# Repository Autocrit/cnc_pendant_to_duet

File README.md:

# CNC Pendant D-Sub connector to Duet PCB

## Overview

The aim for this PCB was to simplify the connection of a CNC pendant to a Duet 2 or 3, and to provide a disconnect at the electronics enclosure.

It follows the wiring diagram and instructions at [Duet3D CNC Pendant Documentation](https://docs.duet3d.com/User_manual/Connecting_hardware/IO_CNC_Pendant).

## Notes

1. Other CNC pendants may have different pin arrangements. Some differences could be fixed in firmware; others only by modifying the PCB.
1. This PCB was tested with a Duet 3, but not with a Duet 2 or a PanelDue.
1. There is a small change needed to the Arduino firmware. 
1. I don't know what I'm doing. Use at your own risk.
1. There's a pin labelled *iO.out* on the PCB in these photos. That's a mistake and its corrected to *dout* in the KiCad project.

## Ordering

Production files are at `./kicad/production/cnc_pendant_to_duet.zip`. In February 2026, 5 boards from JLCPCB cost £3.60 including VAT and delivery to the UK.

## Choice of CNC pendant

I have [this](https://www.aliexpress.com/item/32847286243.html) pendant from [Rattm Motor Store](https://www.aliexpress.com/store/907217) on Aliexpress (the listing says 4-axis but the one I received is 5-axis).

### D-Sub pins

The image below shows a female socket as you look at it:

GND, COM-, and shield are all connected to ground on the PCB.

The connector pinout can be checked against the pads in the pendant.

## Mounting

The PCB can be mounted to the inside of an enclosure using the hex studs of the D‑sub connector. Alternatively, it could be mounted internally with an extension cable.

### Cutout

[DXF](./cad/panel_cutout.dxf)
[PDF](./cad/panel_cutout.pdf)

### PCB dimensions and hole spacing

## Components

| Reference | Description |
|---------- | ------- |
| U1 | Arduino Pro Micro |
| R1 | 1206 SMD 6K8 (6.8kΩ) resistor |
| R2 | 1206 SMD 10K (10kΩ) resistor |
| J1 | 1x4 2.54mm pitch male right-angle (optional) header |
| J2 | 15-pin D-Sub female right-angle (optional) connector with hex screws |

### Arduino Pro Micro (U1)

Use 2 1x12 female headers if the Arduino should be removable.

### Resistors (R1 & R2)

The resistors are optional when connecting to a Duet 3. If omitted, the pads of R1 should be bridged (see image).

### 1x4 header (J1)

The 1x4 pin 2.54mm pitch male header for connecting to a Duet 2 or 3 can be any make or type; a right-angle connector keeps the height low.

Examples are Würth Elektronik WR-WTB [61900411121](https://www.we-online.com/en/components/products/WTB_WR_WTB_2_54_MALE#61900411121) (vertical), 
Würth Elektronik WR-WTB [61900411021](https://www.we-online.com/en/components/products/WTB_WR_WTB_2_54_MALE#61900411021) (horizontal) or Würth Elektronik WR-WTB [61900419521](https://www.we-online.com/en/components/products/WTB_WR_WTB_2_54_MALE#61900419521) (also horizontal).

KF2510 connectors are a cheaper alternative.

### D-Sub connector (J2)

e.g. Würth Elektronik WR-DSUB PCB [618015231121](https://www.we-online.com/en/components/products/INPUT_OUTPUT_WR_DSUB_CONNECTORS_PCB#618015231121).

The mounting‑hole‑to‑board‑edge dimension appears to be a common one; cheaper connectors from, for example, Ebay seem fine.

## Connecting to Duet 2 or 3

This image shows the PCB connected to io.0 on a Duet 3.

See [Connector and spare part numbers](https://docs.duet3d.com/User_manual/Troubleshooting/Parts).

Würth Elektronik WR-WTB 4-pin [61900411621](https://www.we-online.com/en/components/products/WTB_2_54_FEMALE_TERMINAL_HOUSING_6190XX11621#61900411621), Würth Elektronik WR-WTB 5-pin [61900511621](https://www.we-online.com/en/components/products/WTB_2_54_FEMALE_TERMINAL_HOUSING_6190XX11621#61900511621) and Würth Elektronik WR-WTB female crimp [61900113722DEC](https://www.we-online.com/en/components/products/WTB_2_54_FEMALE_CRIMP_CONTACT_619X0113722#61900113722DEC).

## Firmware

### Firmware change

In `CNC-pendant.ino`, change line 221 to:
```
distanceMultiplier = 1;
```

The reason for this is that there is no X1 pin (or signal) and the code is unable to detect that X1 is selected. Initialising `distanceMultiplier` to `1` instead of `0` solves that.

Note that the firmware is unable to control the pendant's LED (for example, to turn it off on an emergency stop) because there is no LED+ signal.

## Config

The Duet3D pendant documentation doesn't mention that serial communication needs to be enabled on io0 on Duet 3. For example:
```
; Accessories
M575 P1 S1 B57600 ; CNC pendant support
```

## Modifying the PCB for a different pinout

Anyone familiar with KiCad or PCB design should ignore this.
1. In the Schematic Editor, change labels on the DA-15 socket as necessary.
1. In the PCB Editor, *Tools->Update PCB from Schematic...*
1. Delete all vias and tracks with *Edit->Global Deletions...->Tracks & vias*
1. I would then cheat and use the *Freerouting* plugin, followed by some clean up (it  leaves unconnected tracks and other easily-fixed issues).
1. Use *Inspect->Design Rules Checker* to help find problems.
1. I used the *Fabrication Toolkit* plugin to generate files for JLCPCB. As its going to be an unassembled board, only the ZIP file is important.

I can help if you know the pinout but don't want to dive into KiCad.

## Adding a D-Sub connector to the "standard" CNC pendant

## TODO
- test with Duet 2
- test with PanelDue 
- test with more than one CNC pendant
- add pins for PanelDue wiring (if that would be useful)

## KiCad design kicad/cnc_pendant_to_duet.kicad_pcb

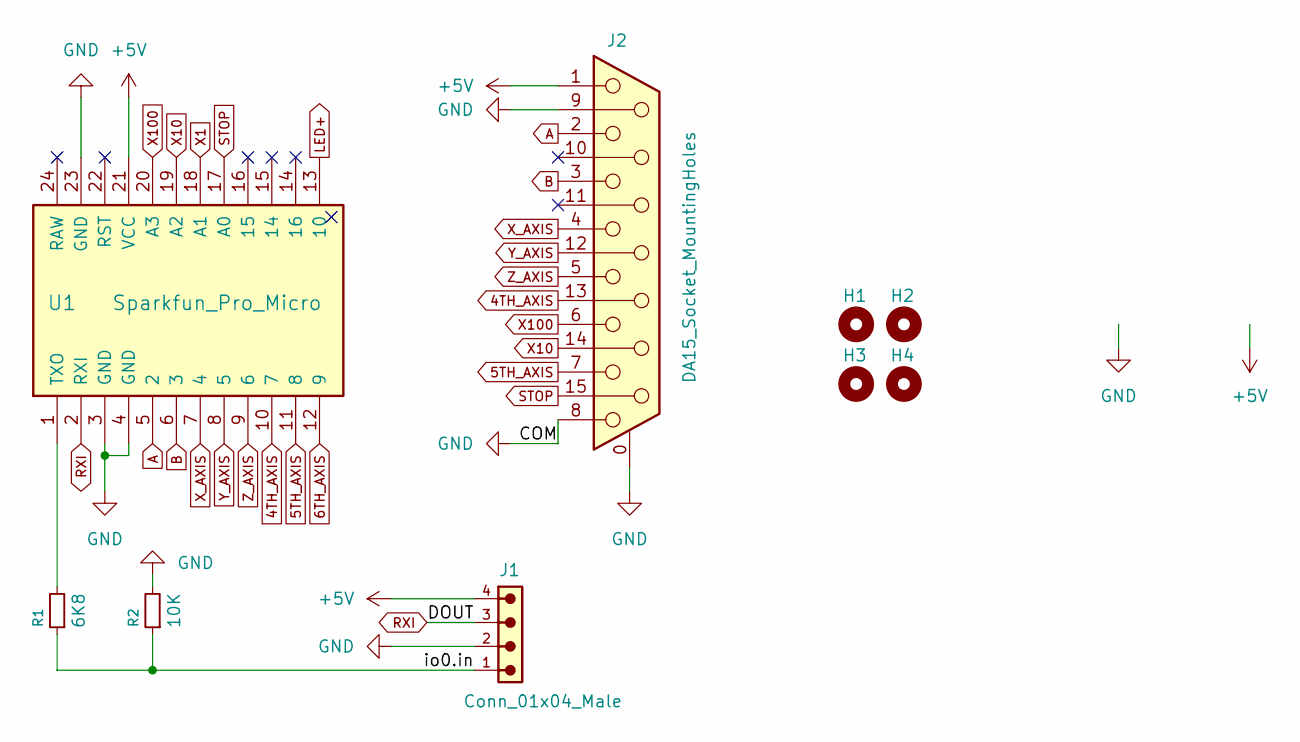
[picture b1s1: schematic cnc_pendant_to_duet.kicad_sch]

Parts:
H1, H2, H3, H4: MountingHole; MountingHole_3.2mm_M3_DIN965_Pad
J1: Conn_01x04_Male; 61900411021
J2: DA15_Socket_MountingHoles; DSUB-15_Socket_Horizontal_P2.77x2.84mm_EdgePinOffset7.70mm_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
R1: 6K8; R_1206_3216Metric_Pad1.30x1.75mm_HandSolder
R2: 10K; R_1206_3216Metric_Pad1.30x1.75mm_HandSolder
U1: Sparkfun_Pro_Micro

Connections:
4TH_AXIS: J2.13, U1.10 (7)
5TH_AXIS: J2.7, U1.11 (8)
6TH_AXIS: U1.12 (9)
+5V: J1.4, J2.1, U1.21 (VCC)
/io0.in: J1.1, R1.1, R2.1
A: J2.2, U1.5 (2)
B: J2.3, U1.6 (3)
GND: J1.2, J2.0 (PAD), J2.8, J2.9, R2.2, U1.3 (GND), U1.4 (GND), U1.23 (GND)
LED+: U1.13 (10)
unnamed: R1.2, U1.1 (TXO)
RXI: J1.3, U1.2 (RXI)
STOP: J2.15, U1.17 (A0)
X1: U1.18 (A1)
X10: J2.14, U1.19 (A2)
X100: J2.6, U1.20 (A3)
X_AXIS: J2.4, U1.7 (4)
Y_AXIS: J2.12, U1.8 (5)
Z_AXIS: J2.5, U1.9 (6)

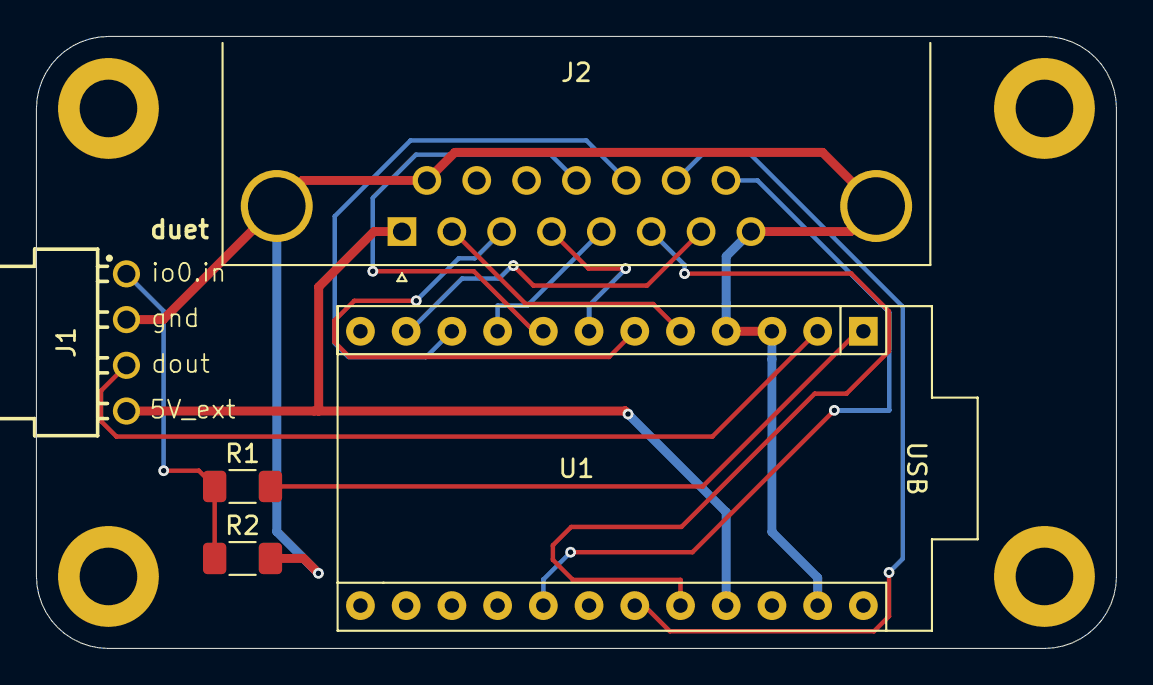
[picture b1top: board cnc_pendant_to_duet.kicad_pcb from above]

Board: 2 copper layers, 60.0 x 34.0 mm, 9 parts (0 on the bottom side), 15 nets.

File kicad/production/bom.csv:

Designator,Footprint,Quantity,Value,LCSC Part #
J1,61900411021,1,Conn_01x04_Male,
J2,DSUB-15_Socket_Horizontal_P2.77x2.84mm_EdgePinOffset7.70mm_Housed_MountingHolesOffset9.12mm,1,DA15_Socket_MountingHoles,
R1,1206,1,6K8,
R2,1206,1,10K,
U1,Sparkfun_Pro_Micro,1,Sparkfun_Pro_Micro,

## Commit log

2026-02-04 readme
2026-02-05 KiCad initial commit
2026-02-05 renaming
2026-02-06 Confusion over connecting to Duet and PanelDue
    Change to silkscreens
2026-02-07 production files
2026-02-11 10k resistor and Arduino pin 4 to GND
    PCB not updated from schematic at this point
2026-02-15 Switched to global labels in schematic. Updated PCB
    Not tested
2026-02-15 Corrected i0.in to io0.in on silkscreen
    Regenerated production files
2026-02-15 Silkscreen text fixes. Regenerated production files
2026-03-05 Rename to cnc_pendant_to_duet
